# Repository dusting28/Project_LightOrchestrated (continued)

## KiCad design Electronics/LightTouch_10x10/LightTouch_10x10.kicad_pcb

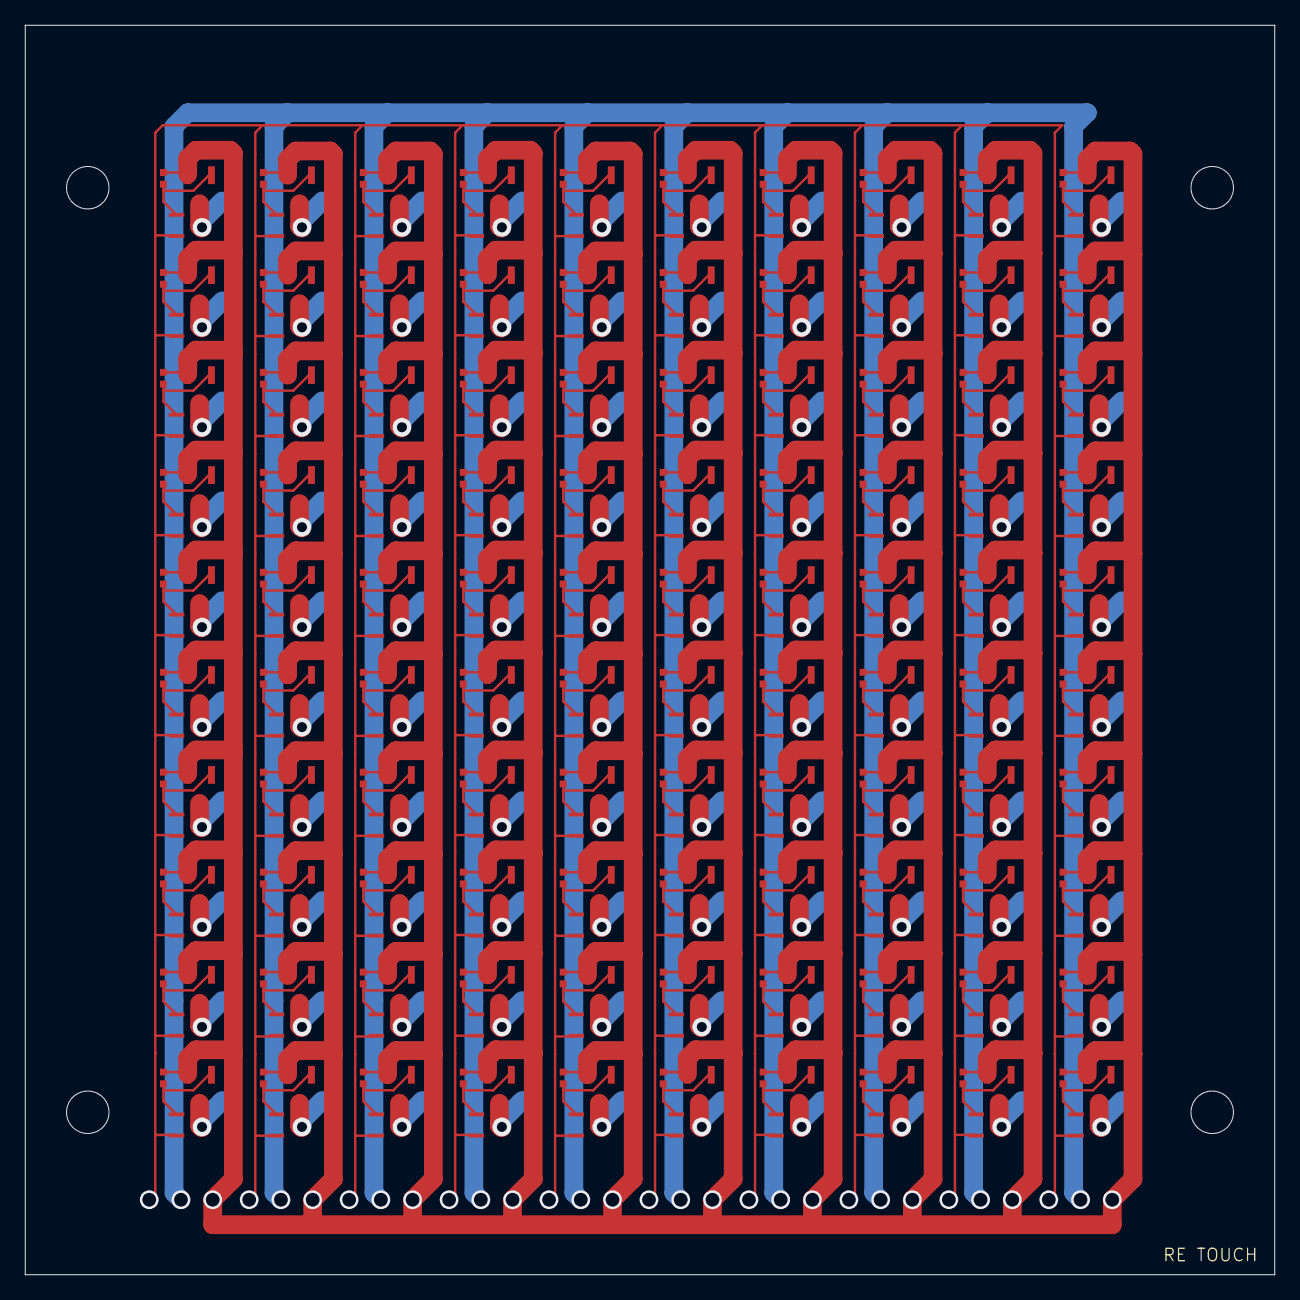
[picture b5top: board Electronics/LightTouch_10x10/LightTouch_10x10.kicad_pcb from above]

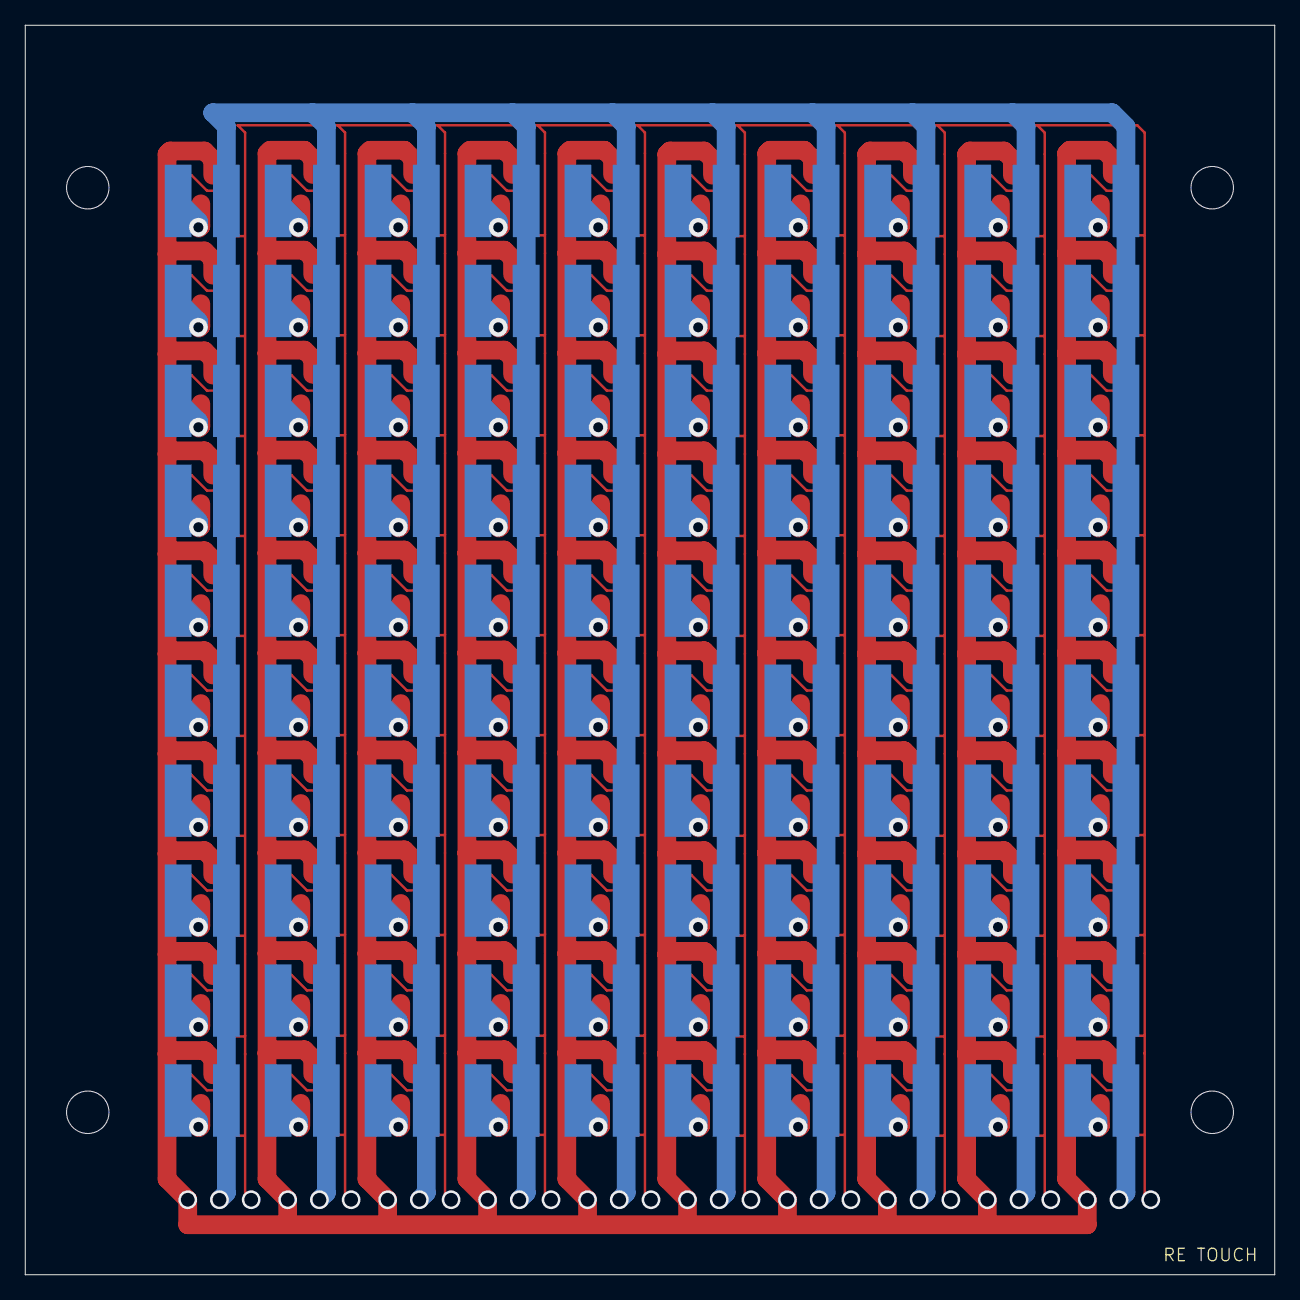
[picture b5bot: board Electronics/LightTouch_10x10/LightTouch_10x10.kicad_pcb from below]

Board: 2 copper layers, 100.0 x 100.0 mm, 400 parts (100 on the bottom side), 203 nets.

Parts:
L1, L2, L3, L4, L5, L6, L7, L8, L9, L10, L11, L12, L13, L14, L15, L16, L17, L18, L19, L20, L21, L22, L23, L24, L25, L26, L27, L28, L29, L30, L31, L32, L33, L34, L35, L36, L37, L38, L39, L40, L41, L42, L43, L44, L45, L46, L47, L48, L49, L50, L51, L52, L53, L54, L55, L56, L57, L58, L59, L60, L61, L62, L63, L64, L65, L66, L67, L68, L69, L70, L71, L72, L73, L74, L75, L76, L77, L78, L79, L80, L81, L82, L83, L84, L85, L86, L87, L88, L89, L90, L91, L92, L93, L94, L95, L96, L97, L98, L99, L100: SDR0604- 821KL; IND_BOURNS_SDR0604
Q1, Q3, Q5, Q7, Q9, Q11, Q13, Q15, Q17, Q19, Q21, Q23, Q25, Q27, Q29, Q31, Q33, Q35, Q37, Q39, Q41, Q43, Q45, Q47, Q49, Q51, Q53, Q55, Q57, Q59, Q61, Q63, Q65, Q67, Q69, Q71, Q73, Q75, Q77, Q79, Q81, Q83, Q85, Q87, Q89, Q91, Q93, Q95, Q97, Q99, Q101, Q103, Q105, Q107, Q109, Q111, Q113, Q115, Q117, Q119, Q121, Q123, Q125, Q127, Q129, Q131, Q133, Q135, Q137, Q139, Q141, Q143, Q145, Q147, Q149, Q151, Q153, Q155, Q157, Q159, Q161, Q163, Q165, Q167, Q169, Q171, Q173, Q175, Q177, Q179, Q181, Q183, Q185, Q187, Q189, Q191, Q193, Q195, Q197, Q199: RPM-075PTT86; TRANS_RPM-075P_ROM
Q2, Q4, Q6, Q8, Q10, Q12, Q14, Q16, Q18, Q20, Q22, Q24, Q26, Q28, Q30, Q32, Q34, Q36, Q38, Q40, Q42, Q44, Q46, Q48, Q50, Q52, Q54, Q56, Q58, Q60, Q62, Q64, Q66, Q68, Q70, Q72, Q74, Q76, Q78, Q80, Q82, Q84, Q86, Q88, Q90, Q92, Q94, Q96, Q98, Q100, Q102, Q104, Q106, Q108, Q110, Q112, Q114, Q116, Q118, Q120, Q122, Q124, Q126, Q128, Q130, Q132, Q134, Q136, Q138, Q140, Q142, Q144, Q146, Q148, Q150, Q152, Q154, Q156, Q158, Q160, Q162, Q164, Q166, Q168, Q170, Q172, Q174, Q176, Q178, Q180, Q182, Q184, Q186, Q188, Q190, Q192, Q194, Q196, Q198, Q200: RQ5E070BNTCL; TRANS_RDR005N_ROM
R1, R2, R3, R4, R5, R6, R7, R8, R9, R10, R11, R12, R13, R14, R15, R16, R17, R18, R19, R20, R21, R22, R23, R24, R25, R26, R27, R28, R29, R30, R31, R32, R33, R34, R35, R36, R37, R38, R39, R40, R41, R42, R43, R44, R45, R46, R47, R48, R49, R50, R51, R52, R53, R54, R55, R56, R57, R58, R59, R60, R61, R62, R63, R64, R65, R66, R67, R68, R69, R70, R71, R72, R73, R74, R75, R76, R77, R78, R79, R80, R81, R82, R83, R84, R85, R86, R87, R88, R89, R90, R91, R92, R93, R94, R95, R96, R97, R98, R99, R100: CRCW040250K0FKED; RES_CRCW0402_VIS

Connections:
+10V: Q1.2 (C), Q3.2 (C), Q5.2 (C), Q7.2 (C), Q9.2 (C), Q11.2 (C), Q13.2 (C), Q15.2 (C), Q17.2 (C), Q19.2 (C), Q21.2 (C), Q23.2 (C), Q25.2 (C), Q27.2 (C), Q29.2 (C), Q31.2 (C), Q33.2 (C), Q35.2 (C), Q37.2 (C), Q39.2 (C), Q41.2 (C), Q43.2 (C), Q45.2 (C), Q47.2 (C), Q49.2 (C), Q51.2 (C), Q53.2 (C), Q55.2 (C), Q57.2 (C), Q59.2 (C), Q61.2 (C), Q63.2 (C), Q65.2 (C), Q67.2 (C), Q69.2 (C), Q71.2 (C), Q73.2 (C), Q75.2 (C), Q77.2 (C), Q79.2 (C), Q81.2 (C), Q83.2 (C), Q85.2 (C), Q87.2 (C), Q89.2 (C), Q91.2 (C), Q93.2 (C), Q95.2 (C), Q97.2 (C), Q99.2 (C), Q101.2 (C), Q103.2 (C), Q105.2 (C), Q107.2 (C), Q109.2 (C), Q111.2 (C), Q113.2 (C), Q115.2 (C), Q117.2 (C), Q119.2 (C), Q121.2 (C), Q123.2 (C), Q125.2 (C), Q127.2 (C), Q129.2 (C), Q131.2 (C), Q133.2 (C), Q135.2 (C), Q137.2 (C), Q139.2 (C), Q141.2 (C), Q143.2 (C), Q145.2 (C), Q147.2 (C), Q149.2 (C), Q151.2 (C), Q153.2 (C), Q155.2 (C), Q157.2 (C), Q159.2 (C), Q161.2 (C), Q163.2 (C), Q165.2 (C), Q167.2 (C), Q169.2 (C), Q171.2 (C), Q173.2 (C), Q175.2 (C), Q177.2 (C), Q179.2 (C), Q181.2 (C), Q183.2 (C), Q185.2 (C), Q187.2 (C), Q189.2 (C), Q191.2 (C), Q193.2 (C), Q195.2 (C), Q197.2 (C), Q199.2 (C)
+20V: L1.1, L2.1, L3.1, L4.1, L5.1, L6.1, L7.1, L8.1, L9.1, L10.1, L11.1, L12.1, L13.1, L14.1, L15.1, L16.1, L17.1, L18.1, L19.1, L20.1, L21.1, L22.1, L23.1, L24.1, L25.1, L26.1, L27.1, L28.1, L29.1, L30.1, L31.1, L32.1, L33.1, L34.1, L35.1, L36.1, L37.1, L38.1, L39.1, L40.1, L41.1, L42.1, L43.1, L44.1, L45.1, L46.1, L47.1, L48.1, L49.1, L50.1, L51.1, L52.1, L53.1, L54.1, L55.1, L56.1, L57.1, L58.1, L59.1, L60.1, L61.1, L62.1, L63.1, L64.1, L65.1, L66.1, L67.1, L68.1, L69.1, L70.1, L71.1, L72.1, L73.1, L74.1, L75.1, L76.1, L77.1, L78.1, L79.1, L80.1, L81.1, L82.1, L83.1, L84.1, L85.1, L86.1, L87.1, L88.1, L89.1, L90.1, L91.1, L92.1, L93.1, L94.1, L95.1, L96.1, L97.1, L98.1, L99.1, L100.1
GND: Q2.2 (S), Q4.2 (S), Q6.2 (S), Q8.2 (S), Q10.2 (S), Q12.2 (S), Q14.2 (S), Q16.2 (S), Q18.2 (S), Q20.2 (S), Q22.2 (S), Q24.2 (S), Q26.2 (S), Q28.2 (S), Q30.2 (S), Q32.2 (S), Q34.2 (S), Q36.2 (S), Q38.2 (S), Q40.2 (S), Q42.2 (S), Q44.2 (S), Q46.2 (S), Q48.2 (S), Q50.2 (S), Q52.2 (S), Q54.2 (S), Q56.2 (S), Q58.2 (S), Q60.2 (S), Q62.2 (S), Q64.2 (S), Q66.2 (S), Q68.2 (S), Q70.2 (S), Q72.2 (S), Q74.2 (S), Q76.2 (S), Q78.2 (S), Q80.2 (S), Q82.2 (S), Q84.2 (S), Q86.2 (S), Q88.2 (S), Q90.2 (S), Q92.2 (S), Q94.2 (S), Q96.2 (S), Q98.2 (S), Q100.2 (S), Q102.2 (S), Q104.2 (S), Q106.2 (S), Q108.2 (S), Q110.2 (S), Q112.2 (S), Q114.2 (S), Q116.2 (S), Q118.2 (S), Q120.2 (S), Q122.2 (S), Q124.2 (S), Q126.2 (S), Q128.2 (S), Q130.2 (S), Q132.2 (S), Q134.2 (S), Q136.2 (S), Q138.2 (S), Q140.2 (S), Q142.2 (S), Q144.2 (S), Q146.2 (S), Q148.2 (S), Q150.2 (S), Q152.2 (S), Q154.2 (S), Q156.2 (S), Q158.2 (S), Q160.2 (S), Q162.2 (S), Q164.2 (S), Q166.2 (S), Q168.2 (S), Q170.2 (S), Q172.2 (S), Q174.2 (S), Q176.2 (S), Q178.2 (S), Q180.2 (S), Q182.2 (S), Q184.2 (S), Q186.2 (S), Q188.2 (S), Q190.2 (S), Q192.2 (S), Q194.2 (S), Q196.2 (S), Q198.2 (S), Q200.2 (S), R1.2, R2.2, R3.2, R4.2, R5.2, R6.2, R7.2, R8.2, R9.2, R10.2, R11.2, R12.2, R13.2, R14.2, R15.2, R16.2, R17.2, R18.2, R19.2, R20.2, R21.2, R22.2, R23.2, R24.2, R25.2, R26.2, R27.2, R28.2, R29.2, R30.2, R31.2, R32.2, R33.2, R34.2, R35.2, R36.2, R37.2, R38.2, R39.2, R40.2, R41.2, R42.2, R43.2, R44.2, R45.2, R46.2, R47.2, R48.2, R49.2, R50.2, R51.2, R52.2, R53.2, R54.2, R55.2, R56.2, R57.2, R58.2, R59.2, R60.2, R61.2, R62.2, R63.2, R64.2, R65.2, R66.2, R67.2, R68.2, R69.2, R70.2, R71.2, R72.2, R73.2, R74.2, R75.2, R76.2, R77.2, R78.2, R79.2, R80.2, R81.2, R82.2, R83.2, R84.2, R85.2, R86.2, R87.2, R88.2, R89.2, R90.2, R91.2, R92.2, R93.2, R94.2, R95.2, R96.2, R97.2, R98.2, R99.2, R100.2
unnamed: Q1.1 (E), Q2.1 (G), R1.1
unnamed: L1.2, Q2.3 (D)
unnamed: Q3.1 (E), Q4.1 (G), R2.1
unnamed: L2.2, Q4.3 (D)
unnamed: Q5.1 (E), Q6.1 (G), R3.1
unnamed: L3.2, Q6.3 (D)
unnamed: Q7.1 (E), Q8.1 (G), R4.1
unnamed: L4.2, Q8.3 (D)
unnamed: L5.2, Q10.3 (D)
unnamed: Q9.1 (E), Q10.1 (G), R5.1
unnamed: Q11.1 (E), Q12.1 (G), R6.1
unnamed: L6.2, Q12.3 (D)
unnamed: Q13.1 (E), Q14.1 (G), R7.1
unnamed: L7.2, Q14.3 (D)
unnamed: Q15.1 (E), Q16.1 (G), R8.1
unnamed: L8.2, Q16.3 (D)
unnamed: Q17.1 (E), Q18.1 (G), R9.1
unnamed: L9.2, Q18.3 (D)
unnamed: Q19.1 (E), Q20.1 (G), R10.1
unnamed: L10.2, Q20.3 (D)
unnamed: Q21.1 (E), Q22.1 (G), R11.1
unnamed: L11.2, Q22.3 (D)
unnamed: Q23.1 (E), Q24.1 (G), R12.1
unnamed: L12.2, Q24.3 (D)
unnamed: Q25.1 (E), Q26.1 (G), R13.1
unnamed: L13.2, Q26.3 (D)
unnamed: Q27.1 (E), Q28.1 (G), R14.1
unnamed: L14.2, Q28.3 (D)
unnamed: Q29.1 (E), Q30.1 (G), R15.1
unnamed: L15.2, Q30.3 (D)
unnamed: Q31.1 (E), Q32.1 (G), R16.1
unnamed: L16.2, Q32.3 (D)
unnamed: Q33.1 (E), Q34.1 (G), R17.1
unnamed: L17.2, Q34.3 (D)
unnamed: Q35.1 (E), Q36.1 (G), R18.1
unnamed: L18.2, Q36.3 (D)
unnamed: Q37.1 (E), Q38.1 (G), R19.1
unnamed: L19.2, Q38.3 (D)
unnamed: Q39.1 (E), Q40.1 (G), R20.1
unnamed: L20.2, Q40.3 (D)
unnamed: Q41.1 (E), Q42.1 (G), R21.1
unnamed: L21.2, Q42.3 (D)
unnamed: Q43.1 (E), Q44.1 (G), R22.1
unnamed: L22.2, Q44.3 (D)
unnamed: Q45.1 (E), Q46.1 (G), R23.1
unnamed: L23.2, Q46.3 (D)
unnamed: Q47.1 (E), Q48.1 (G), R24.1
unnamed: L24.2, Q48.3 (D)
unnamed: Q49.1 (E), Q50.1 (G), R25.1
unnamed: L25.2, Q50.3 (D)
unnamed: Q51.1 (E), Q52.1 (G), R26.1
unnamed: L26.2, Q52.3 (D)
unnamed: Q53.1 (E), Q54.1 (G), R27.1
unnamed: L27.2, Q54.3 (D)
unnamed: Q55.1 (E), Q56.1 (G), R28.1
unnamed: L28.2, Q56.3 (D)
unnamed: Q57.1 (E), Q58.1 (G), R29.1
unnamed: L29.2, Q58.3 (D)
unnamed: Q59.1 (E), Q60.1 (G), R30.1
unnamed: L30.2, Q60.3 (D)
unnamed: Q61.1 (E), Q62.1 (G), R31.1
unnamed: L31.2, Q62.3 (D)
unnamed: Q63.1 (E), Q64.1 (G), R32.1
unnamed: L32.2, Q64.3 (D)
unnamed: Q65.1 (E), Q66.1 (G), R33.1
unnamed: L33.2, Q66.3 (D)
unnamed: Q67.1 (E), Q68.1 (G), R34.1
unnamed: L34.2, Q68.3 (D)
unnamed: Q69.1 (E), Q70.1 (G), R35.1
unnamed: L35.2, Q70.3 (D)
unnamed: Q71.1 (E), Q72.1 (G), R36.1
unnamed: L36.2, Q72.3 (D)
unnamed: Q73.1 (E), Q74.1 (G), R37.1
unnamed: L37.2, Q74.3 (D)
unnamed: Q75.1 (E), Q76.1 (G), R38.1
unnamed: L38.2, Q76.3 (D)
unnamed: Q77.1 (E), Q78.1 (G), R39.1
unnamed: L39.2, Q78.3 (D)
unnamed: Q79.1 (E), Q80.1 (G), R40.1
unnamed: L40.2, Q80.3 (D)
unnamed: Q81.1 (E), Q82.1 (G), R41.1
unnamed: L41.2, Q82.3 (D)
unnamed: Q83.1 (E), Q84.1 (G), R42.1
unnamed: L42.2, Q84.3 (D)
unnamed: Q85.1 (E), Q86.1 (G), R43.1
unnamed: L43.2, Q86.3 (D)
unnamed: Q87.1 (E), Q88.1 (G), R44.1
unnamed: L44.2, Q88.3 (D)
unnamed: Q89.1 (E), Q90.1 (G), R45.1
unnamed: L45.2, Q90.3 (D)
unnamed: Q91.1 (E), Q92.1 (G), R46.1
unnamed: L46.2, Q92.3 (D)
unnamed: Q93.1 (E), Q94.1 (G), R47.1
unnamed: L47.2, Q94.3 (D)
unnamed: Q95.1 (E), Q96.1 (G), R48.1
unnamed: L48.2, Q96.3 (D)
unnamed: Q97.1 (E), Q98.1 (G), R49.1
unnamed: L49.2, Q98.3 (D)
unnamed: L50.2, Q100.3 (D)
unnamed: Q99.1 (E), Q100.1 (G), R50.1
unnamed: Q101.1 (E), Q102.1 (G), R51.1
unnamed: L51.2, Q102.3 (D)
unnamed: Q103.1 (E), Q104.1 (G), R52.1
unnamed: L52.2, Q104.3 (D)
unnamed: Q105.1 (E), Q106.1 (G), R53.1
unnamed: L53.2, Q106.3 (D)
unnamed: Q107.1 (E), Q108.1 (G), R54.1
unnamed: L54.2, Q108.3 (D)
unnamed: Q109.1 (E), Q110.1 (G), R55.1
unnamed: L55.2, Q110.3 (D)
unnamed: Q111.1 (E), Q112.1 (G), R56.1
unnamed: L56.2, Q112.3 (D)
unnamed: Q113.1 (E), Q114.1 (G), R57.1
unnamed: L57.2, Q114.3 (D)
unnamed: Q115.1 (E), Q116.1 (G), R58.1
unnamed: L58.2, Q116.3 (D)
unnamed: Q117.1 (E), Q118.1 (G), R59.1
unnamed: L59.2, Q118.3 (D)
unnamed: Q119.1 (E), Q120.1 (G), R60.1
unnamed: L60.2, Q120.3 (D)
unnamed: Q121.1 (E), Q122.1 (G), R61.1
unnamed: L61.2, Q122.3 (D)
unnamed: Q123.1 (E), Q124.1 (G), R62.1
unnamed: L62.2, Q124.3 (D)
unnamed: Q125.1 (E), Q126.1 (G), R63.1
unnamed: L63.2, Q126.3 (D)
unnamed: Q127.1 (E), Q128.1 (G), R64.1
unnamed: L64.2, Q128.3 (D)
unnamed: Q129.1 (E), Q130.1 (G), R65.1
unnamed: L65.2, Q130.3 (D)
unnamed: Q131.1 (E), Q132.1 (G), R66.1
unnamed: L66.2, Q132.3 (D)
unnamed: Q133.1 (E), Q134.1 (G), R67.1
unnamed: L67.2, Q134.3 (D)
unnamed: Q135.1 (E), Q136.1 (G), R68.1
unnamed: L68.2, Q136.3 (D)
unnamed: Q137.1 (E), Q138.1 (G), R69.1
unnamed: L69.2, Q138.3 (D)
unnamed: Q139.1 (E), Q140.1 (G), R70.1
unnamed: L70.2, Q140.3 (D)
unnamed: Q141.1 (E), Q142.1 (G), R71.1
unnamed: L71.2, Q142.3 (D)
unnamed: Q143.1 (E), Q144.1 (G), R72.1
unnamed: L72.2, Q144.3 (D)
unnamed: Q145.1 (E), Q146.1 (G), R73.1
unnamed: L73.2, Q146.3 (D)
unnamed: Q147.1 (E), Q148.1 (G), R74.1
unnamed: L74.2, Q148.3 (D)
unnamed: Q149.1 (E), Q150.1 (G), R75.1
unnamed: L75.2, Q150.3 (D)
unnamed: Q151.1 (E), Q152.1 (G), R76.1
unnamed: L76.2, Q152.3 (D)
unnamed: Q153.1 (E), Q154.1 (G), R77.1
unnamed: L77.2, Q154.3 (D)
unnamed: Q155.1 (E), Q156.1 (G), R78.1
unnamed: L78.2, Q156.3 (D)
unnamed: Q157.1 (E), Q158.1 (G), R79.1
unnamed: L79.2, Q158.3 (D)
unnamed: Q159.1 (E), Q160.1 (G), R80.1
unnamed: L80.2, Q160.3 (D)
unnamed: Q161.1 (E), Q162.1 (G), R81.1
unnamed: L81.2, Q162.3 (D)
unnamed: Q163.1 (E), Q164.1 (G), R82.1
unnamed: L82.2, Q164.3 (D)
unnamed: Q165.1 (E), Q166.1 (G), R83.1
unnamed: L83.2, Q166.3 (D)
unnamed: Q167.1 (E), Q168.1 (G), R84.1
unnamed: L84.2, Q168.3 (D)
unnamed: Q169.1 (E), Q170.1 (G), R85.1
unnamed: L85.2, Q170.3 (D)
unnamed: Q171.1 (E), Q172.1 (G), R86.1
unnamed: L86.2, Q172.3 (D)
unnamed: Q173.1 (E), Q174.1 (G), R87.1
unnamed: L87.2, Q174.3 (D)
unnamed: Q175.1 (E), Q176.1 (G), R88.1
unnamed: L88.2, Q176.3 (D)
unnamed: Q177.1 (E), Q178.1 (G), R89.1
unnamed: L89.2, Q178.3 (D)
unnamed: Q179.1 (E), Q180.1 (G), R90.1
unnamed: L90.2, Q180.3 (D)
unnamed: Q181.1 (E), Q182.1 (G), R91.1
unnamed: L91.2, Q182.3 (D)
unnamed: Q183.1 (E), Q184.1 (G), R92.1
unnamed: L92.2, Q184.3 (D)
unnamed: Q185.1 (E), Q186.1 (G), R93.1
unnamed: L93.2, Q186.3 (D)
unnamed: Q187.1 (E), Q188.1 (G), R94.1
unnamed: L94.2, Q188.3 (D)
unnamed: Q189.1 (E), Q190.1 (G), R95.1
unnamed: L95.2, Q190.3 (D)
unnamed: Q191.1 (E), Q192.1 (G), R96.1
unnamed: L96.2, Q192.3 (D)
unnamed: Q193.1 (E), Q194.1 (G), R97.1
unnamed: L97.2, Q194.3 (D)
unnamed: Q195.1 (E), Q196.1 (G), R98.1
unnamed: L98.2, Q196.3 (D)
unnamed: Q197.1 (E), Q198.1 (G), R99.1
unnamed: L99.2, Q198.3 (D)
unnamed: Q199.1 (E), Q200.1 (G), R100.1
unnamed: L100.2, Q200.3 (D)

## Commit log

2024-11-15 Added Measurement Code
2024-11-15 Added files from lab desktop
2024-11-15 Moved folders around
2024-11-15 Testing github
2024-11-25 Small changes to file architecture
2024-11-25 Small design modifications
2025-01-14 DesignV1
2025-01-27 Version3 of Design
2025-02-03 Dynamics Model of System
2025-02-26 small change
2025-02-26 Added Paul's CAD
2025-02-26 Customized Version Added
2025-02-27 Started PCB Design
2025-03-02 Max patches for thermal stress test
2025-03-02 Edited Version 2 to Mimic Paul Prototype
2025-03-03 Version 2 updated
2025-03-03 temp files removed
2025-03-15 Pulsed Data Collected
2025-03-16 Additional pulsed measurements
2025-03-16 Momentum-Based Version
2025-03-16 Momentum-based analysis
2025-03-19 Updated CAD to Momentum-Based
2025-03-19 Testing Phototransistor
2025-03-24 Shielding analysis with gaps
2025-03-24 kicad pcb
2025-03-24 Moved max patches
2025-03-26 Finished 10x10 design
2025-03-26 Electronics Measurements
2025-03-26 Made drawing for machine shop
2025-03-27 Added silkscreen layer
2025-03-27 Small CAD updates
2025-03-29 Moved CAD around
2025-03-31 Created new engineering drawing for Josh
2025-04-03 PCB design with larger MOSFET
2025-04-05 Edited CAD
2025-04-07 PCB design with new MOSFETs
2025-04-09 Finished 10x10 PCB with new mosfets
2025-04-17 Created figures 1-3 and rendered PCB CAD
2025-04-17 Edited CAD to make 9 mm shielding holes
2025-04-22 Captured Data with LED source
2025-04-24 Compression Test Completed
2025-04-24 Redesigned with Nonlinear Spring
2025-04-26 Restructured Files
2025-05-08 Thermal measurements taken
2025-05-08 More LED control from Arduino
2025-05-20 Updated CAD
2025-05-20 COMSOL EM forces with shielding
2025-05-23 Created light patterns for laptop
2025-05-23 Added 10x10 design for linear guide
2025-05-31 Analyzed Proportional Data
2025-05-31 Gathered pulsed data for proportional control and thermal measurements
2025-06-02 Data for Lab Meeting
2025-06-02 COMSOL Elastic
2025-06-02 Optical Cavity Design
2025-06-02 Minor changes
2025-06-03 Re-aligned positioning holes in PCB design
2025-06-04 Thermal Calibration
2025-06-05 Calibrated thermal measurements
2025-06-18 Finished Dynamic Measurements
    Verify thermal results before moving forward.
2025-06-18 Analyzed Thermal Data
2025-06-18 Took last mechanical measurements
2025-06-25 CAD for Perception Study
2025-06-25 Generated Figures for Dynamic Measurements and Thermal Analysis
2025-06-26 Finished thermal figure
2025-07-04 Modification to troubleshoot device reliability issues
2025-07-07 Finished first pilot study with Cole
2025-07-07 Designs for troubleshooting device
2025-07-10 Finished Perception Study
2025-07-10 Scripts for Analyzing Perception Data
2025-07-11 Updated participant contact info
2025-07-11 Generated subfigures for perception study
2025-07-13 Finished Editing Figures
2025-07-18 Added Moving Line
2025-07-18 Implemented round 1 of Yon feedback
2025-07-18 Output Moving Line
2025-07-25 Magnitude Study + Video Documentation
2025-07-26 Added premiere movies
2025-08-01 Added new metrics for localization
